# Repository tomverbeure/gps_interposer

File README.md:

* Install PICO SDK

```
export PICO_SDK_PATH="/home/tom/projects/pico-sdk"
```

For DSView:
```
sudo apt install -y qtcreator qtbase5-dev qt5-qmake cmake
```

```
sudo apt install cmake gcc-arm-none-eabi libnewlib-arm-none-eabi libstdc++-arm-none-eabi-newlib
cd ~/projects
git clone git@github.com:raspberrypi/pico-sdk.git
cd pico-sdk
git submodule update --init --recursive
```

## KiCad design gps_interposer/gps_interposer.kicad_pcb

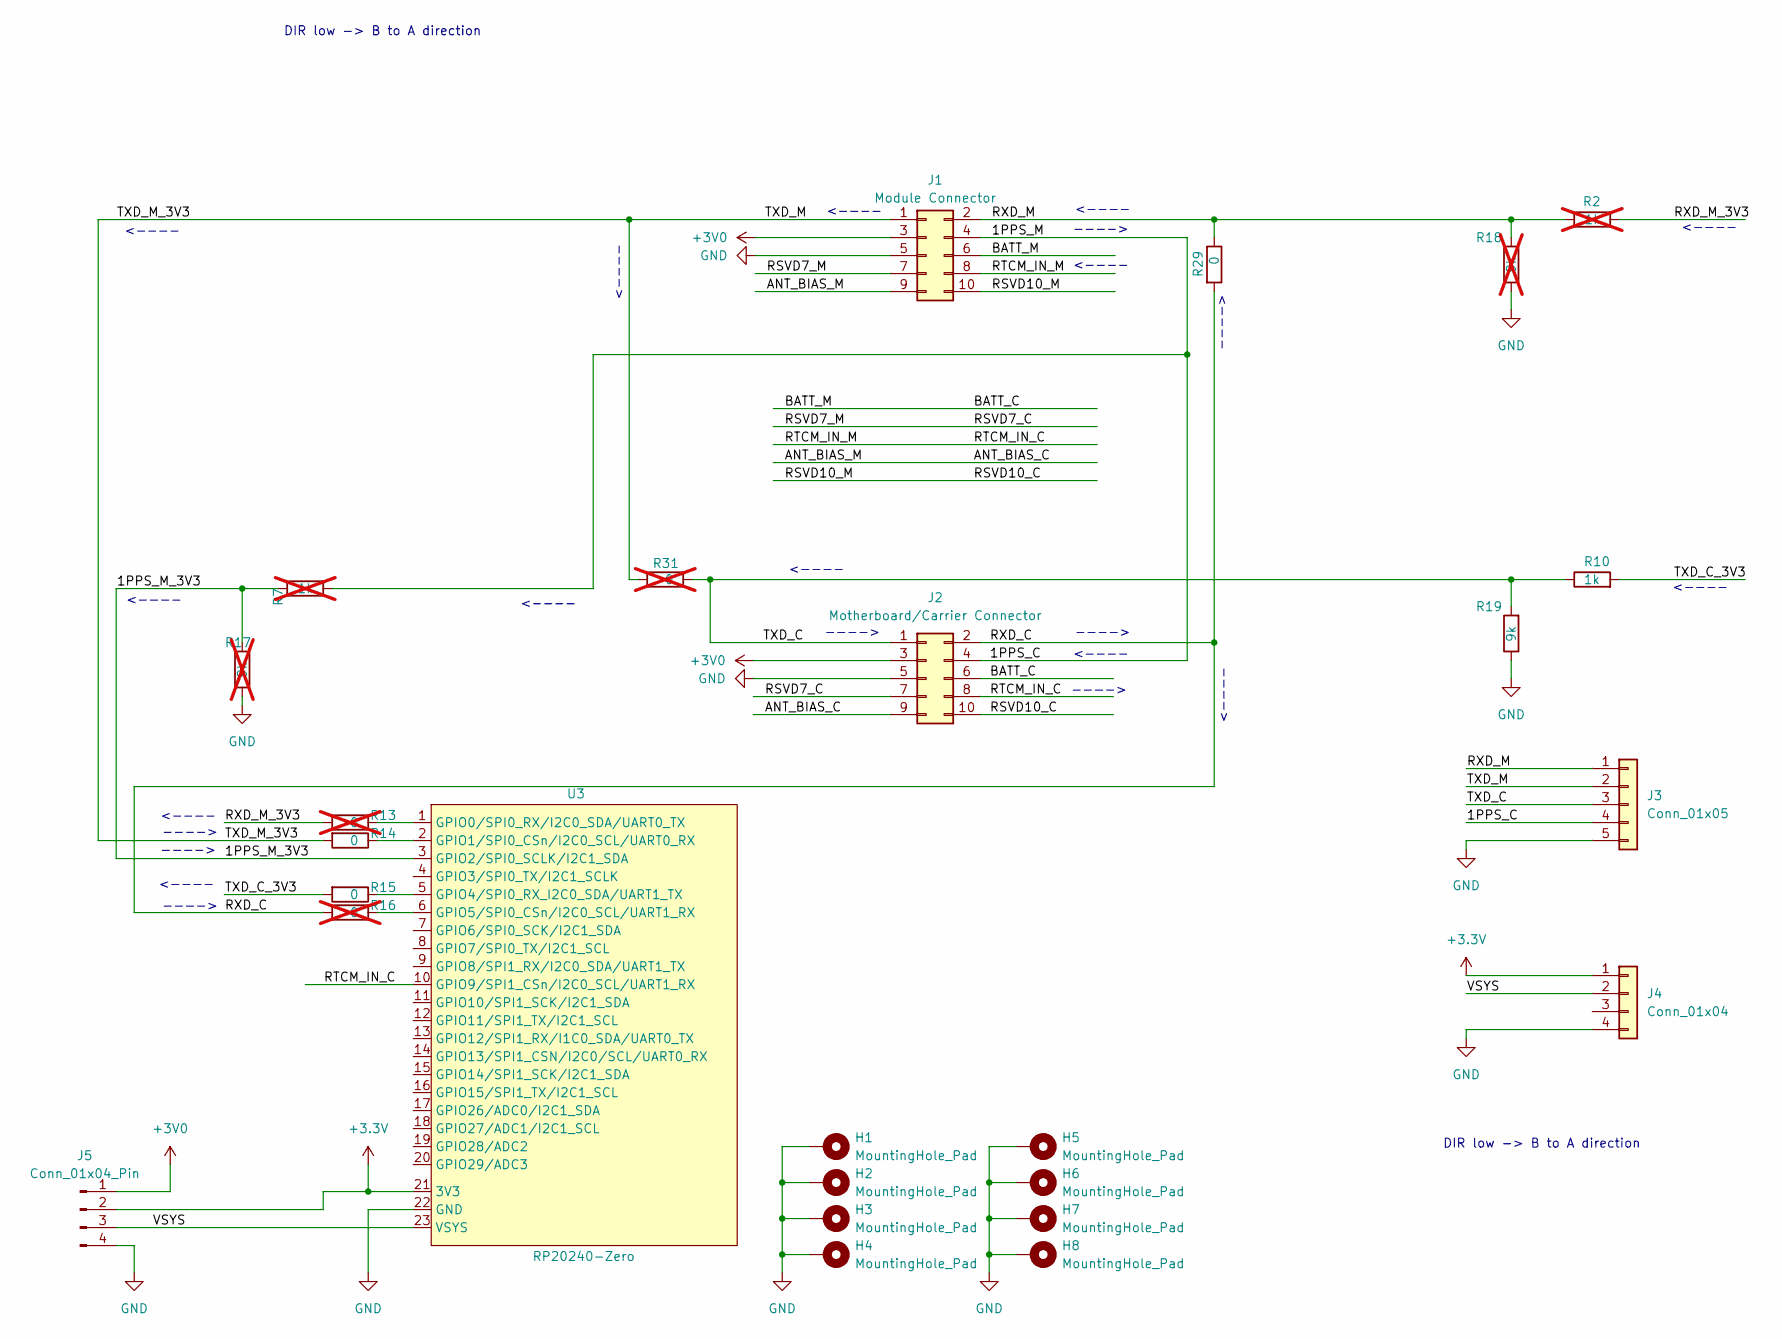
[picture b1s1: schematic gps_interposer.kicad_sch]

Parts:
H1, H2, H3, H4, H5, H6, H7, H8: MountingHole_Pad; MountingHole_2.5mm_3.9mm_Pad_TopBottom_1
J1: Module Connector; PinSocket_2x05_P1.27mm_Vertical_SMD
J2: Motherboard/Carrier Connector; PinHeader_2x05_P1.27mm_Vertical_SMD
J3: Conn_01x05; PinHeader_1x05_P2.54mm_Vertical_SMD_Pin1Left
J4: Conn_01x04; PinHeader_1x04_P2.54mm_Horizontal
J5: Conn_01x04_Pin; PinHeader_1x04_P2.54mm_Horizontal
R2, R7: 1k; R_0603_1608Metric_Pad0.98x0.95mm_HandSolder; not fitted
R10: 1k; R_0603_1608Metric_Pad0.98x0.95mm_HandSolder
R13, R16, R31: 0; R_0603_1608Metric_Pad0.98x0.95mm_HandSolder; not fitted
R14, R15, R29: 0; R_0603_1608Metric_Pad0.98x0.95mm_HandSolder
R17, R18: 9k; R_0603_1608Metric_Pad0.98x0.95mm_HandSolder; not fitted
R19: 9k; R_0603_1608Metric_Pad0.98x0.95mm_HandSolder
U3: RP20240-Zero; RP2040-Zero

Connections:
+3.3V: J4.1, J5.2, U3.21 (3V3)
+3V0: J1.3, J2.3, J5.1
/1PPS_C: J1.4, J2.4, J3.4, R7.1
/1PPS_M_3V3: R7.2, R17.2, U3.3 (GPIO2/SPI0_SCLK/I2C1_SDA)
/ANT_BIAS_C: J1.9, J2.9
/BATT_C: J1.6, J2.6
/RSVD7_C: J1.7, J2.7
/RSVD10_C: J1.10, J2.10
/RTCM_IN_C: J1.8, J2.8, U3.10 (GPIO9/SPI1_CSn/I2C0_SCL/UART1_RX)
/RXD_C: J2.2, R16.2, R29.2
/RXD_M: J1.2, J3.1, R2.2, R18.2, R29.1
/RXD_M_3V3: R2.1, R13.2
/TXD_C: J2.1, J3.3, R10.1, R19.2, R31.1
/TXD_C_3V3: R10.2, R15.2
/TXD_M: J1.1, J3.2, R14.2, R31.2
/VSYS: J4.2, J5.3, U3.23 (VSYS)
GND: H1.1, H2.1, H3.1, H4.1, H5.1, H6.1, H7.1, H8.1, J1.5, J2.5, J3.5, J4.4, J5.4, R17.1, R18.1, R19.1, U3.22 (GND)
unnamed: R13.1, U3.1 (GPIO0/SPI0_RX/I2C0_SDA/UART0_TX)
unnamed: R14.1, U3.2 (GPIO1/SPI0_CSn/I2C0_SCL/UART0_RX)
unnamed: R15.1, U3.5 (GPIO4/SPI0_RX_I2C0_SDA/UART1_TX)
unnamed: R16.1, U3.6 (GPIO5/SPI0_CSn/I2C0_SCL/UART1_RX)

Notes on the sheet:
<----
---->
DIR low -> B to A direction

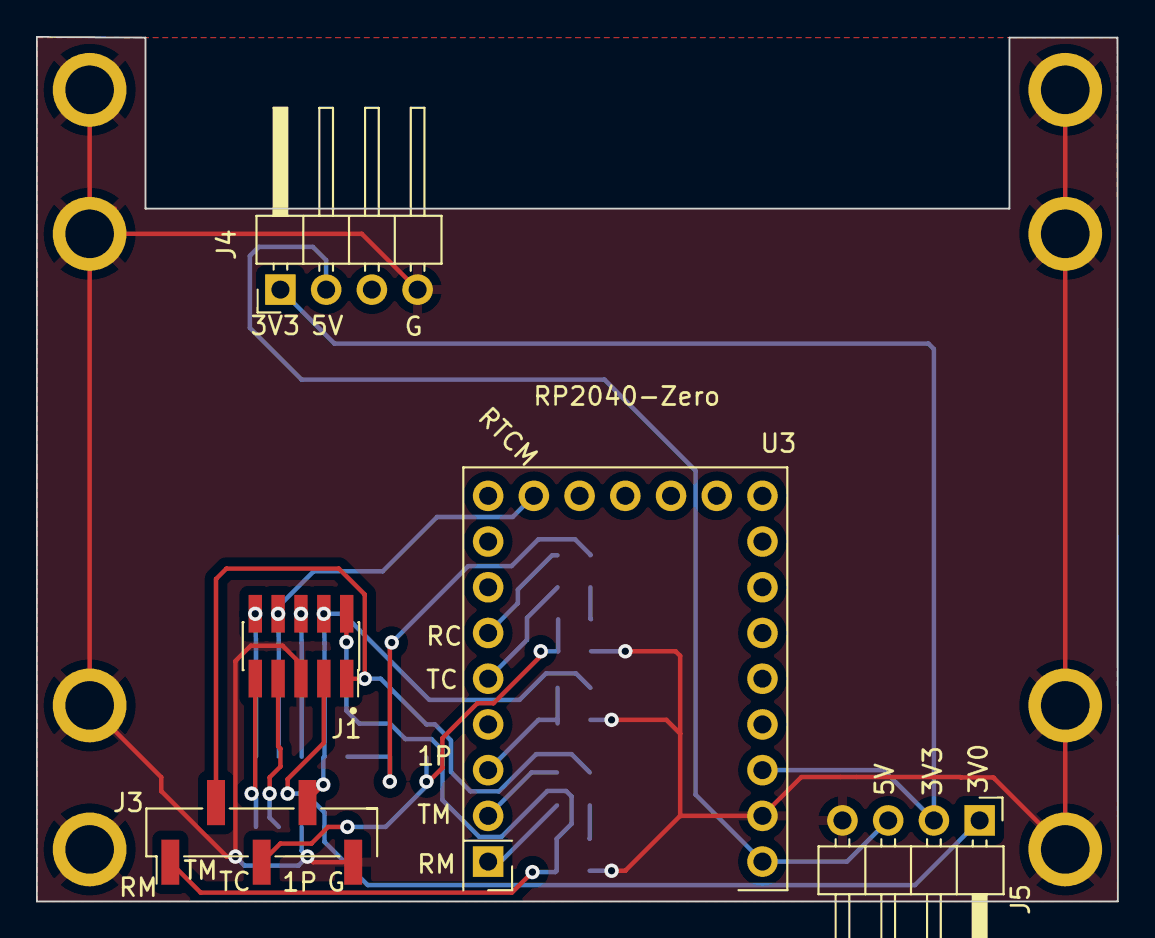
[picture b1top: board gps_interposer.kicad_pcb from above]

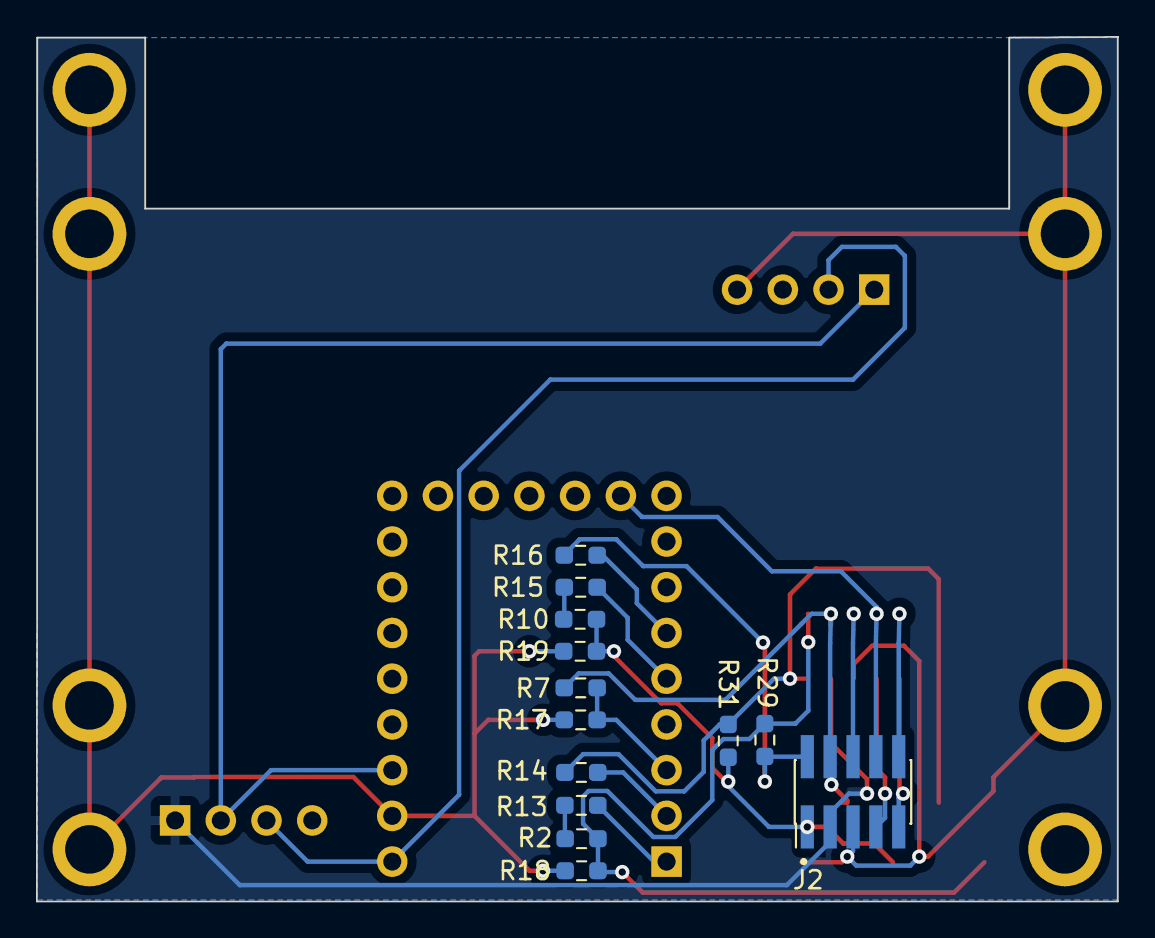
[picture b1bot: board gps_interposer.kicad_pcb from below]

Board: 2 copper layers, 60.1 x 48.0 mm, 26 parts (13 on the bottom side), 21 nets.

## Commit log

2024-04-07 Start.
2024-04-08 PCB almost done.
2024-04-09 PCB ready.
2024-04-29 Buildable hello world.
2024-04-29 STDIO to USB.
2024-04-29 hello_world -> gps_interposer
2024-04-29 Write to STDIO USB, UART0 and UART1.
2024-04-30 Generic packet decoder.
2024-05-04 Decode one message.
2024-05-04 Check checksum.
2024-05-04 Recalce checksum.
2024-05-04 Date conversion.
2024-05-05 PCB v2.
2024-05-05 V2 gerbers.
2024-05-05 Update checksum in modified packet.
2024-05-05 Fix adding 1024 weeks.
2024-05-05 Additional connectors.
2024-05-19 Dir reorg.
2024-05-19 Build instructions.
2024-05-19 Fix formatting.
2024-05-19 rp2024_v2 - refactor M12Parser. WIP.
2024-05-27 Blink LED. Mark correct resistors as installed.
2024-05-27 Move WS2812 to ./shared.
2024-05-29 Tab.
2024-05-29 Fix date correction.
2024-05-31 Modify Ha, Hn and Co messages.
2024-05-31 Wire up RX interposer.
2024-05-31 Don't send dummy message.
2024-05-31 rev2: pass-through RX and TX.
2024-05-31 rev2: send @@Gb command.
2024-06-01 Paced transmit.
2024-06-01 Move Gb command until after first initialization burst.
2024-06-03 Decode Ha resp packet.
